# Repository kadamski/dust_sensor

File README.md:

## Howto: dust sensor HW

### Overview

This project is an open hardware project aimed for intermediate software developers and electronics engineers (as well as others, provided they've got someone of the electronics background at hand).
The idea behind the project is to provide _**cheap and easy to build**_ **dust sensor** that will measure **PM2.5, PM10**, Temperature and Humidity, display those on the LCD and be able to send the values onto dedicated server (e.g. http get).

Here's how the prototype looks like. 

We've succesfully build few of those already. Using simple plexi enclosure. And they work like a charm.

### Parts list

In order to build one of your own, you'll need following pieces of HW:
* **PCB**
In this git one can find _kicad-ESP8266_ and _GERBERS_ directories. This is a schematics for PCB used in our project.
Please refer to [PCB](#pcb) section, there will be more about that there.
Approx cost: <$2.5 (~$25 for 10 PCBs order)

* **PCD8544** 48x84 pixels LCD display
Please note, that there're few versions of the Nokia 5110 LCD boards. One will need one with following order of GOLDPINs:
  * 1 - RST
  * 2 - CE
  * 3 - DC
  * 4 - DIN
  * 5 - CLK
  * 6 - VCC
  * 7 - LIGHT
  * 8 - GND
  
As for example one in the middle in following pictures:

Other two will require either some type of wire instead of just goldpins to connect proper inputs/outputs (the one on the left) or may cause the backlight of the LCD to be always ON (one on the right; not sure why though).
Approx cost: <$2

* **AM2302/DHT22** digital-output relative humidity & temperature sensor

 This is an easy to get item. One can also consider using lower-cost lower-precission DHT11. 
 Further reading: [Digital relative humidity & temperature sensor AM2302/DHT22](https://cdn-shop.adafruit.com/datasheets/Digital+humidity+and+temperature+sensor+AM2302.pdf)
 
 Approx cost: <$2

* **SDS011** Laser PM2.5 Sensor

 This is the most expensive and most important part of the device. It's easily available on the internet. Best prices spoted in China ;-) 
 Further reading: [Laser PM2.5 Sensor specification](http://inovafitness.com/software/SDS011%20laser%20PM2.5%20sensor%20specification-V1.3.pdf)
 
 Approx cost: $22-$25
 
* **ESP8266-12F** (optionally ESP8266-12E) MCU

 Please be carefull when buying ESP8266, a _heart of the device_. You'll need very specific version of it: ESP-12F. You can optionally replace it with ESP-12E, which is better available in Europe, but it is not FCC approved and may cause some problems due to this and the fact it's got a little bit worse antena. More details: [ESP8266 Wiki](https://en.wikipedia.org/wiki/ESP8266)
 
 Approx cost: <$2
 
* **PCF8574AT**: Remote 8-bit I/O expander for I2C-bus with interrupt

 Expander is needed, hence we've used all the GPIO ports of ESP-12E/F. This is due to the fact, that the SDS011 uses UART to communicate with the external world (needs 2 pins of ESP) and there's LCD & THT on top of that. The extender is talking with the ESP using only two pins over I2C protocol.
 
 Approx cost: TODO
 
* Other minor **electronic parts**: 
  * AP1117-3.3 LDO Voltage Regulator (SMD) - Low drop fixed positive voltage regulator 3,3V
  * Capacitors (SMD): C1 = 100uF, C2 = C4 = 10uF, 
  * Resistors (SMD): R1 = R2 = R3 = R6 = R7 = R8 = 10k, R4 = 220k, R5 = 100k 
  * Tact Switch 6x6, 13mm (THT) x 3 pcs
  * PINs: 
    * Single Row Male 2.54 Right Angle Pin Header Connector Strip
    * Single Row Male 2.54 Breakable Pin Header Connector Strip
    * Single Row Female 2.54 mm Pin Header Connector Strip
  * 2.54mm Jumper Cap (Short Circuit Cap) x 4 pcs
  * Female Micro USB socket type B
    
 Approx (sum) cost: <$2

* **Optional**: Plexi enclosure, screws, etc - to keep it all together

 This is optional, but we've put the drawings for both bottom and top of the enclosure in this git. You may find it [here](https://github.com/kadamski/dust_sensor/tree/master/enclosure)
 
 Approx cost: <$2

#### PCB

##### Schematics & ordering of the PCB

I hope you're using Linux, it will be much easier this way. In this git we've prepared PCB schematics that are ready to just be sent over to a PCB factory of some sort. In order to browse those, exprort, etc one will need to install kicad.

  sudo apt-get install kicad

Now please clone the dust_sensor git

  git clone https://github.com/kadamski/dust_sensor.git

Launch kicad, then select _File->Open Project_. Now select _dust_sensor.pro_ from the repository cloned above.

Most of the PCB factories will accept Gerber files. There's already a directory named GERBERS in the git with ready to go files, however you may want to change sth, etc, then just double click on dust_sensor.kicad_pcb in kicad, which will launch _Pcbnew_. Use _File->Fabrication Outputs_ to get what you need.

Just get a quote and order. It looks that chineese factories seem to be cheaper than US/EU based ones. For some strange reason ;-)

##### PCB - Known issues

* The footprint for DHT22 is wrong, meaning the distance between holes is to small, causing one must bent DHT's legs in ordert ot put them into the holes. Also holes are a little bit to small in diameter, same comes for the size of the pads. Be carefull when soldering. This will be fixed in next revision.
* There're at the moment 4 jumpers on the board, that is
 * PWR - used for serial current metering
 * LCD_RST - put to enable LCD, otherwise LCD's RST is connected to RST switch
 * DHT - one can connect DHT to ESP-12E/F (via Exetender) or directly to free GPIO pin (for debug purposes)
 * DEEP - jumper used to enable Deep Sleep mode of the ESP8266, otherwise the device will be always on. Note that in deep sleep it'll take much less current (good for battery powered applications, but the backlight of the LCD will only work during time, when the ESP is not in sleep, i.e. when it measures dust once every _interval_).
 
 These are no longer needed and most, but DEEP, will be removed in next revision of the board.

### Putting things together

Yes, it means **soldering**. This is what we would like You to have in your hands in the end. If you're experienced in soldering it should take you no more than 30 minutes. Let's start...

FRONT (do not bother little yellow cable fixtures, you won't need them, this is just my nasty broken board)

BACK

### Getting firmware & flashing

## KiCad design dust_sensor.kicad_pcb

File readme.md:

## Howto: dust sensor HW

### Overview

This project is an open hardware project aimed for intermediate software developers and electronics engineers (as well as others, provided they've got someone of the electronics background at hand).
The idea behind the project is to provide _**cheap and easy to build**_ **dust sensor** that will measure **PM2.5, PM10**, Temperature and Humidity, display those on the LCD and be able to send the values onto dedicated server (e.g. http get).

Here's how the prototype looks like. 

We've succesfully build few of those already. Using simple plexi enclosure. And they work like a charm.

### Parts list

In order to build one of your own, you'll need following pieces of HW:
* **PCB**
In this git one can find _kicad-ESP8266_ and _GERBERS_ directories. This is a schematics for PCB used in our project.
Please refer to [PCB](#pcb) section, there will be more about that there.
Approx cost: <$2.5 (~$25 for 10 PCBs order)

* **PCD8544** 48x84 pixels LCD display
Please note, that there're few versions of the Nokia 5110 LCD boards. One will need one with following order of GOLDPINs:
  * 1 - RST
  * 2 - CE
  * 3 - DC
  * 4 - DIN
  * 5 - CLK
  * 6 - VCC
  * 7 - LIGHT
  * 8 - GND
  
As for example one in the middle in following pictures:

Other two will require either some type of wire instead of just goldpins to connect proper inputs/outputs (the one on the left) or may cause the backlight of the LCD to be always ON (one on the right; not sure why though).
Approx cost: <$2

* **AM2302/DHT22** digital-output relative humidity & temperature sensor

 This is an easy to get item. One can also consider using lower-cost lower-precission DHT11. 
 Further reading: [Digital relative humidity & temperature sensor AM2302/DHT22](https://cdn-shop.adafruit.com/datasheets/Digital+humidity+and+temperature+sensor+AM2302.pdf)
 
 Approx cost: <$2

* **SDS011** Laser PM2.5 Sensor

 This is the most expensive and most important part of the device. It's easily available on the internet. Best prices spoted in China ;-) 
 Further reading: [Laser PM2.5 Sensor specification](http://inovafitness.com/software/SDS011%20laser%20PM2.5%20sensor%20specification-V1.3.pdf)
 
 Approx cost: $22-$25
 
* **ESP8266-12F** (optionally ESP8266-12E) MCU

 Please be carefull when buying ESP8266, a _heart of the device_. You'll need very specific version of it: ESP-12F. You can optionally replace it with ESP-12E, which is better available in Europe, but it is not FCC approved and may cause some problems due to this and the fact it's got a little bit worse antena. More details: [ESP8266 Wiki](https://en.wikipedia.org/wiki/ESP8266)
 
 Approx cost: <$2
 
* **PCF8574AT**: Remote 8-bit I/O expander for I2C-bus with interrupt

 Expander is needed, hence we've used all the GPIO ports of ESP-12E/F. This is due to the fact, that the SDS011 uses UART to communicate with the external world (needs 2 pins of ESP) and there's LCD & THT on top of that. The extender is talking with the ESP using only two pins over I2C protocol.
 
 Approx cost: TODO
 
* Other minor **electronic parts**: 
  * LD33 (SMD) - Low drop fixed positive voltage regulator 3,3V
  * Capacitors (SMD): C1 = 100uF, C2 = C4 = 10uF, 
  * Resistors (SMD): R1 = R2 = R3 = R6 = R7 = R8 = 10k, R4 = 220k, R5 = 100k 
  * Tact Switch 6x6, 13mm (THT): 3x
  * PINs: 
    * Single Row Male 2.54 Right Angle Pin Header Connector Strip
    * Single Row Male 2.54 Breakable Pin Header Connector Strip
    * Single Row Female 2.54 mm Pin Header Connector Strip
  * 2.54mm Jumper Cap (Short Circuit Cap) x 4
  * Female Micro USB socket type B
    
 Approx (sum) cost: <$2

* **Optional**: Plexi enclosure, screws, etc - to keep it all together

 This is optional, but we've put the drawings for both bottom and top of the enclosure in this git. You may find it [here](https://github.com/kadamski/dust_sensor/tree/master/enclosure)
 
 Approx cost: <$2

#### PCB

I hope you're using Linux, it will be much easier this way. In this git we've prepared PCB schematics that are ready to just be sent over to a PCB factory of some sort. In order to browse those, exprort, etc one will need to install kicad.

  sudo apt-get install kicad

Now please clone the dust_sensor git

  git clone https://github.com/kadamski/dust_sensor.git

Launch kicad, then select _File->Open Project_. Now select _dust_sensor.pro_ from the repository cloned above.

Most of the PCB factories will accept Gerber files. There's already a directory named GERBERS in the git with ready to go files, however you may want to change sth, etc, then just double click on dust_sensor.kicad_pcb in kicad, which will launch _Pcbnew_. Use _File->Fabrication Outputs_ to get what you need.

Just get a quote and order. It looks that chineese factories seem to be cheaper than US/EU based ones. For some strange reason ;-)

### Putting things together

Yes, it means **soldering**. This is what we would like You to have in your hands in the end. If you're experienced in soldering it should take you no more than 30 minutes. Let's start...

FRONT (do not bother little yellow cable fixtures, you won't need them, this is just my nasty broken board)

BACK

### Getting firmware & flashing

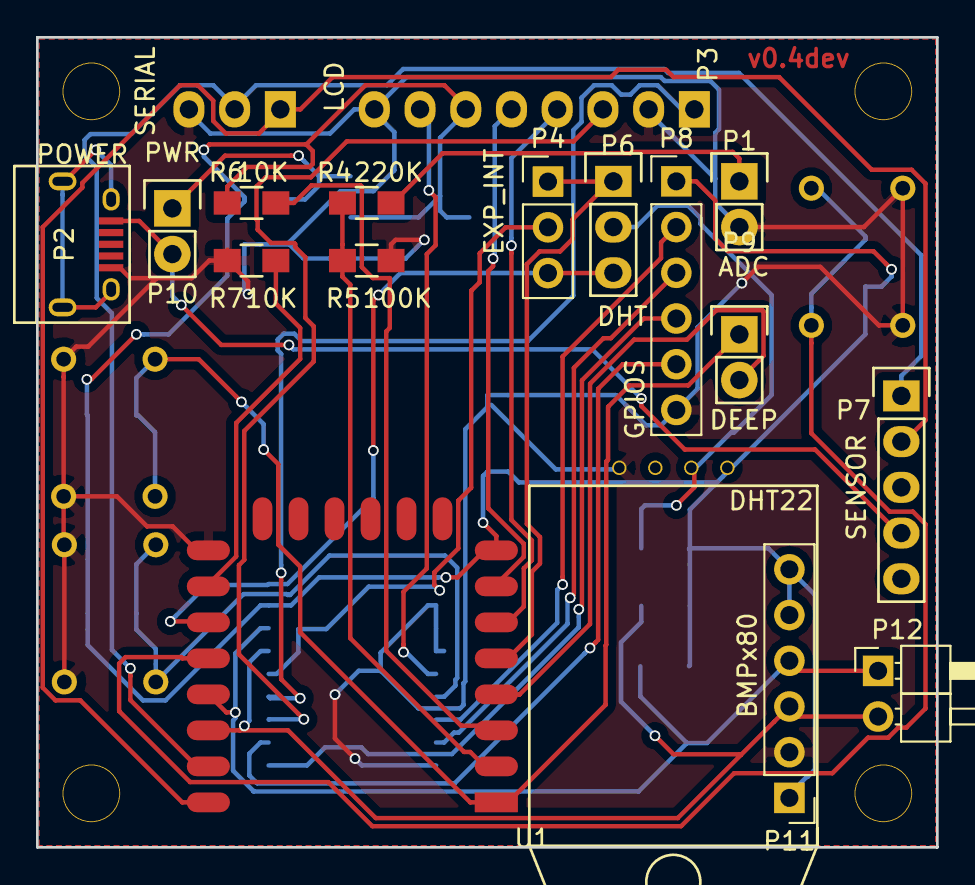
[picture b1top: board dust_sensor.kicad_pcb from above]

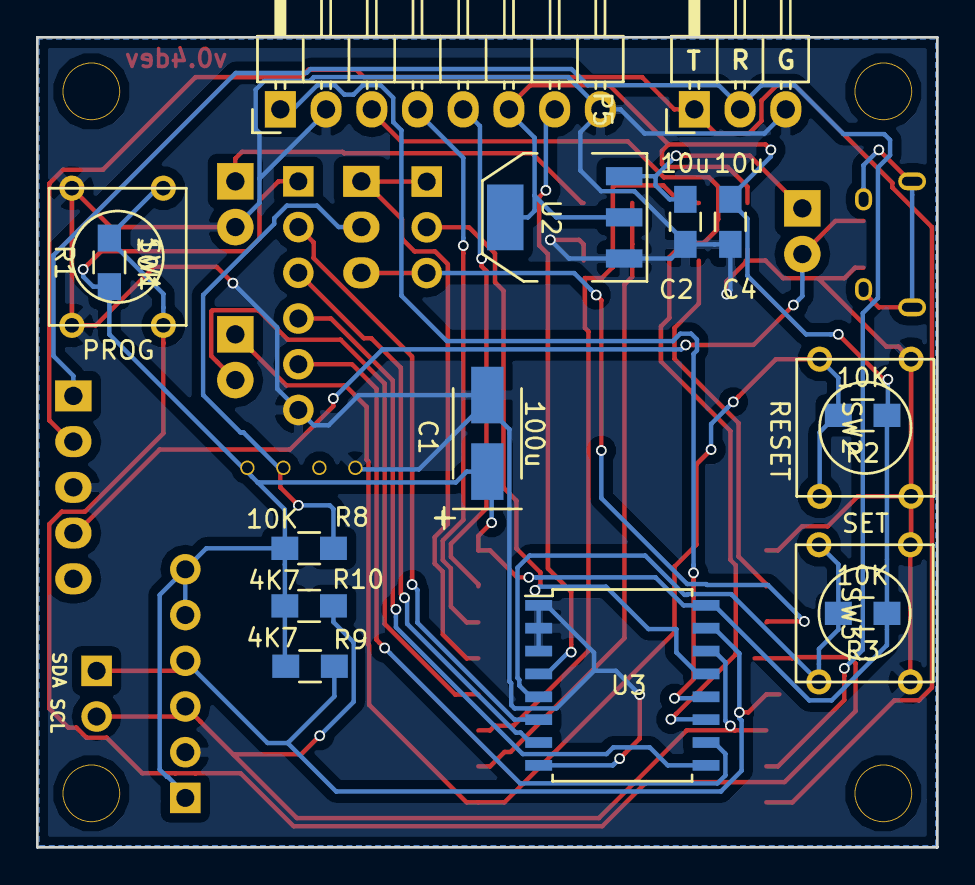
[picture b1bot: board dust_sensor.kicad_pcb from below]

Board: 2 copper layers, 50.0 x 45.0 mm, 32 parts (16 on the bottom side), 29 nets.

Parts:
C1: 100u; TantalC_SizeB_EIA-3528_HandSoldering
C2, C4: 10u; C_0805_HandSoldering
P1: ADC; Pin_Header_Straight_1x02
P2: POWER; USB_Micro-B
P3: LCD; Pin_Header_Angled_1x08
P4: EXP_INT; Pin_Header_Straight_1x03_Pitch2.54mm
P5: SERIAL; Pin_Header_Angled_1x03
P6: DHT; Pin_Header_Straight_1x03
P7: SENSOR; Pin_Header_Straight_1x05
P8: GPIOS; Pin_Header_Straight_1x06_Pitch2.54mm
P9: DEEP; Pin_Header_Straight_1x02
P10: PWR; Pin_Header_Straight_1x02
P11: BMPx80; Pin_Header_Straight_1x06_Pitch2.54mm
P12: I²C; Pin_Header_Angled_1x02_Pitch2.54mm
R1, R2, R3, R6, R7, R8: 10K; R_0805_HandSoldering
R4: 220K; R_0805_HandSoldering
R5: 100K; R_0805_HandSoldering
R9, R10: 4K7; R_0805_HandSoldering
SW1: PROG; SW_PUSH_SMALL
SW2: RESET; SW_PUSH_SMALL
SW3: SET; SW_PUSH_SMALL
U1: ESP-12E
U2: AP1117; SOT-223
U3: PCF8574; SOIC-16_7.5x10.3mm_Pitch1.27mm
U4: DHT22; DHT22_nohole

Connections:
+3V3: C1.1, C4.1, P3.6, P8.1, P11.1, P11.5, P11.6, R1.1, R2.1, R3.1, R6.2, R8.1, R9.1, R10.1, U1.8, U2.2, U2.4, U3.16, U4.1
+5V: P2.1, P7.4, P10.2
ADC: R4.2, R5.1, U1.2
GND: C1.2, C2.2, C4.2, P1.2, P2.5, P3.2, P3.8, P5.3, P7.3, P8.6, P11.2, R5.2, R7.2, SW1.2, SW2.2, SW3.2, U1.15, U2.1, U3.1, U3.2, U3.3, U3.8, U4.4
GPIO2: P4.3, P6.3, U1.17
GPIO14: P4.1, P6.1, U1.5
GPIO16: P9.2, U1.4
LIGHT: P3.7, U3.4
unnamed: C2.1, P10.1, U2.3
unnamed: P1.1, R4.1
unnamed: P3.1, U3.12
unnamed: P3.3, U3.11
unnamed: P3.4, U1.6
unnamed: P3.5, U1.7
unnamed: P4.2, U3.13
unnamed: P6.2, R8.2, U4.2
unnamed: R6.1, U1.3
unnamed: R7.1, U1.16
P2: P8.2, U3.6
P3: P8.3, U3.7
P4: P8.4, U3.9
P5: P8.5, U3.10
PROG: R1.2, SW1.1, U1.18
RESET: P9.1, R2.2, SW2.1, U1.1
RX: P5.2, P7.1, U1.21
SCL: P11.3, P12.2, R10.2, U1.20, U3.14
SDA: P11.4, P12.1, R9.2, U1.19, U3.15
SET: R3.2, SW3.1, U3.5
TX: P5.1, P7.2, U1.22

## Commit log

2016-03-17 Init.
2016-03-18 Add ESP8266 library as submodule
2016-03-18 SCH: Annotate schematic components
2016-03-18 SCH: Fix some DRC errors.
2016-03-18 SCH: Remove unneded PWR_FLAGS for 3.3V and 5V
2016-03-18 SCH: Set components footprints
2016-03-18 dht.lib: add pad numbers to DHT22
2016-03-18 SCH: Add pullup resistor for dht22
2016-03-18 SCH: add values for R2 and R3
2016-03-18 SCH: set footprint for DHT22
2016-03-18 SCH: connector for unassigned gpios
2016-03-18 SCH: set footrpint for GPIO conn and pullup
2016-03-18 PRO: add missing ESP8266 library to fp-lib-table
2016-03-18 SCH: remove ADC pin from GPIO conn
2016-03-18 PCB: initial layout
2016-03-18 lib: add mounting holes
2016-03-18 PCB: bigger board + mounting holes
2016-03-20 SCH, PCB: add 10uF capacitor at 1117 out
2016-03-20 SCH, PCB: add jumper for deep sleep
2016-03-20 PCB: flip LCD connector
2016-03-20 PCB, SCH: add current measure jumper
2016-03-20 SCH, PCB: remove 100uF from 1117 output
2016-03-20 PCB: some better component organization.
2016-03-20 PCB: place some wires
2016-03-20 PCB: complete routing
2016-03-20 PCB: rework labels
2016-03-20 PCB, SCH: Remove hole from DHT22
2016-03-20 Add version label, change holes to 3mm
2016-03-20 PCB: use filled zones for GND
2016-03-20 PCB: gerber settings.
2016-03-20 GRB: v0.1dev
2016-03-20 GBR: Don't add extended header
2016-03-21 PCB: connect unconnected GNDs
2016-03-21 SCH, PCB: Change CH_PD and GPIO15 resistors to 10k
2016-03-21 Use tantalum footprint for 100uF capacitor.
2016-03-21 SCH: cosmetic changes in labels
2016-11-01 GRB: v0.2dev
2017-01-09 enclosure: draft
2017-01-13 Create readme.md
    readmy.md placeholder, to be updated during a day today.
2017-01-13 first update
2017-01-13 Remove images
2017-01-13 [README] Few words about the LCD display
2017-01-13 [README] Parts breakdown
2017-01-13 [README] About putting things together
2017-01-13 [README] Passive electronics & picture update.
2017-01-13 [README] Fixes and updates, jumpers
2017-01-13 [README] Jumper fixture
2017-01-13 [README] One more try to fix jumpers
2017-01-13 [README] Add and fill in README.md (#4)
    First version or README.md that explains how to put all things together.
2017-01-15 Fix DHT22 footprint (hopefully)
2017-01-15 PCB: v0.3dev: change DHT22 footprint
2017-01-15 SCH: remove LCD_RST jumper
2017-01-15 PCB: remove LCD_RST jumper
2017-01-16 PCB: SCH: choose ext_int/dht between GPIO2/GPIO14
2017-01-16 SCH,PCB: Add GND/3.3V to GPIOS header, fix order of pins
2017-01-16 PCB: change version to v0.4dev
2017-01-16 GERBERS: remove, there is no GERBERS for v0.4 yet
2017-01-17 PCB: SCH: Add header for BMP180/280
2017-01-17 SCH: make some space on top
2017-01-17 SCH: PCB: Add external I²C connector
2017-01-18 PCB: SCH: add I²C pullups.
2017-01-18 PCB: traces optimalization
2017-01-18 PCB: small clenups
2017-01-19 Add CorelDraw versions of the files
    Adds CorelDraw files (CDR) in X7 and X8 versions.
2017-02-14 encloure: add DXF version made in QCad
